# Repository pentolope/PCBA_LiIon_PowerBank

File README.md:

# Single-Cell Li-Ion Power Bank

Single-cell Li-ion power bank board: USB-C input, battery charging and protection, and a regulated 5 V output capable of at least 2 A.

This repository holds the design problem for `PCBA_LiIon_PowerBank`, a single-cell Li-ion power bank board. The brief fixes the functional envelope: a USB-C input, battery charging, battery protection, a regulated 5 V output capable of at least 2 A, fuel/status indication, and a pushbutton-controlled output enable. It also states two process constraints — choose an integrated charger/power-path/boost solution where practical, and respect the layout guidance of the selected power ICs while minimizing high-current loop area — and instructs that stated requirements be treated as authoritative. Everything else is open: the brief names no part, vendor, IC, connector, cell, capacity, dimension, charge current, input power level, output-stage topology, stackup, or protection topology, so the architecture and every component choice belong to the design agent. At brief detail 2/5, the correct response is to make and document those decisions from cited evidence rather than to treat any of them as pre-fixed.

> **This board has not been designed.** There is no schematic, no layout and no
> part selection here — only the brief, a reading of the brief, and the
> scaffolding a design run needs. That is the intended state of this repository,
> not a gap in it.

## What the brief fixes, and what it leaves open

The brief pins down 13 requirements and deliberately leaves
19 decisions to whoever designs the board. The `Source` column says
which is which: `brief` is quoted from [BRIEF.md](BRIEF.md), `metadata` comes
from the benchmark catalogue, and `open` means the brief does not fix it.

| Aspect | Value | Source |
|---|---|---|
| Board function | Single-cell Li-ion power bank board | brief |
| Input interface | USB-C input | brief |
| Charging | Battery charging on the board | brief |
| Battery protection | Battery protection required (location and topology unstated) | brief |
| Output rail | Regulated 5 V, capable of at least 2 A | brief |
| Indication | Fuel/status indication (form not specified) | brief |
| User control | Pushbutton-controlled output enable | brief |
| Power IC integration preference | Integrated charger/power-path/boost solution where practical (a preference, with "practical" left undefined) | brief |
| Layout constraint | Follow the selected power ICs' layout guidance; minimize high-current loop area | brief |
| Requirement authority | Stated requirements are authoritative; where the brief is open, the agent makes and documents the decision | brief |
| Toolkit relationship | Repo consumes the shared PCBA_AutoDesignAndTest toolkit; no board-specific logic added to the toolkit | brief |
| Likely layer count | 2 or 4 (stated as "likely" in both the brief header and metadata; fixed by neither) | metadata |
| Category / difficulty / brief detail | power-management; difficulty 2; detail 2 | metadata |
| Primary stressors | charger layout, power-path routing, battery safety, USB-C power | metadata |
| Parts, connectors, cell, mechanics, charge current, input power level, output-stage and protection topology | Not fixed by the brief — design agent's choice | open |

The full split, with the verbatim brief text substantiating every fixed
requirement, is in [board/requirements.md](board/requirements.md) and
machine-readably in [board/requirements.json](board/requirements.json).

**Missing details are design freedom, not permission to fabricate unstated user
requirements.** A choice the brief left open is recorded as a decision, with its
reasoning — never promoted into a requirement.

## Benchmark position

| | |
|---|---|
| Benchmark id | 7 of 32 |
| Category | power-management |
| Difficulty | 2 / 5 |
| Brief detail | 2 / 5 |
| Likely layer count | 2 or 4 |
| Primary stressors | charger layout, power-path routing, battery safety, USB-C power |

This is a difficulty-2, detail-2 power-management board whose stressors are charger layout, power-path routing, battery safety, and USB-C power. It tests whether an agent can turn a short functional brief into a defensible power chain — sizing, selecting, and laying out a charger, a power path, and a 5 V output stage — and whether it can substantiate a 2 A output claim with real datasheet, magnetics, and thermal evidence instead of asserting it. Because the brief names no parts and no mechanics, it equally tests whether the agent keeps its own choices visible as choices rather than smuggling them in as requirements.

This repository is one of thirty-two. The suite, the protocol and the results
live in [PCBA_AutoDesignAndTest_Bench](https://github.com/pentolope/PCBA_AutoDesignAndTest_Bench).

## Repository layout

| Path | Contents |
|---|---|
| `BRIEF.md` | the supplied brief — authoritative, preserved byte for byte, never edited |
| `board/requirements.md` | what the brief fixes, what it leaves open, and where decisions get recorded |
| `board/requirements.json` | the same split, machine-readable, each fixed requirement bound to brief text |
| `board/manifest.template.json` | the toolkit's minimum manifest, pre-filled for this board |
| `board/toolchain.json` | where this board's build finds KiCad and the router |
| `benchmark/metadata.json` | the supplied catalogue entry — category, difficulty, detail, stressors |
| `docs/architecture.md` | the decisions this board must make, as questions, unanswered |
| `docs/sources.md` | the classes of evidence the design will have to cite |
| `docs/status.md` | what exists, what does not, and what is deliberately absent |
| `candidates/` | disposable search output, ignored by Git |
| `.claude/skills/` | the accountability-review skill [CLAUDE.md](CLAUDE.md) requires before a push |
| `tooling/PCBA_AutoDesignAndTest` | the shared verification/routing/release toolkit, as a pinned submodule |

## Getting the repository

The toolkit is a submodule and carries KiCad Routing Tools as a submodule of its
own, so clone recursively:

```bash
git clone --recursive https://github.com/pentolope/PCBA_LiIon_PowerBank.git
```

```bash
git submodule update --init --recursive
```

## Designing the board

Generic verification, routing and release logic is **not** written here. It is
consumed from `tooling/PCBA_AutoDesignAndTest`, which is board-agnostic by
construction and must stay that way; this repository owns the board and nothing
else. Start from
[the toolkit's onboarding guide](tooling/PCBA_AutoDesignAndTest/examples/onboarding.md),
and see [CLAUDE.md](CLAUDE.md) for the rules a design run works under.

```bash
python3 tooling/PCBA_AutoDesignAndTest/run.py preflight
```

## Brief integrity

`BRIEF.md` SHA-256 `a83c2729b4cd3572342d1c0d042245c18bb77970d150b0bb1acddd78cdec8627`

Every quotation in `board/requirements.json` is bound to those exact bytes. If
the brief ever changes, the bindings are stale by construction — which is the
point of recording the digest.

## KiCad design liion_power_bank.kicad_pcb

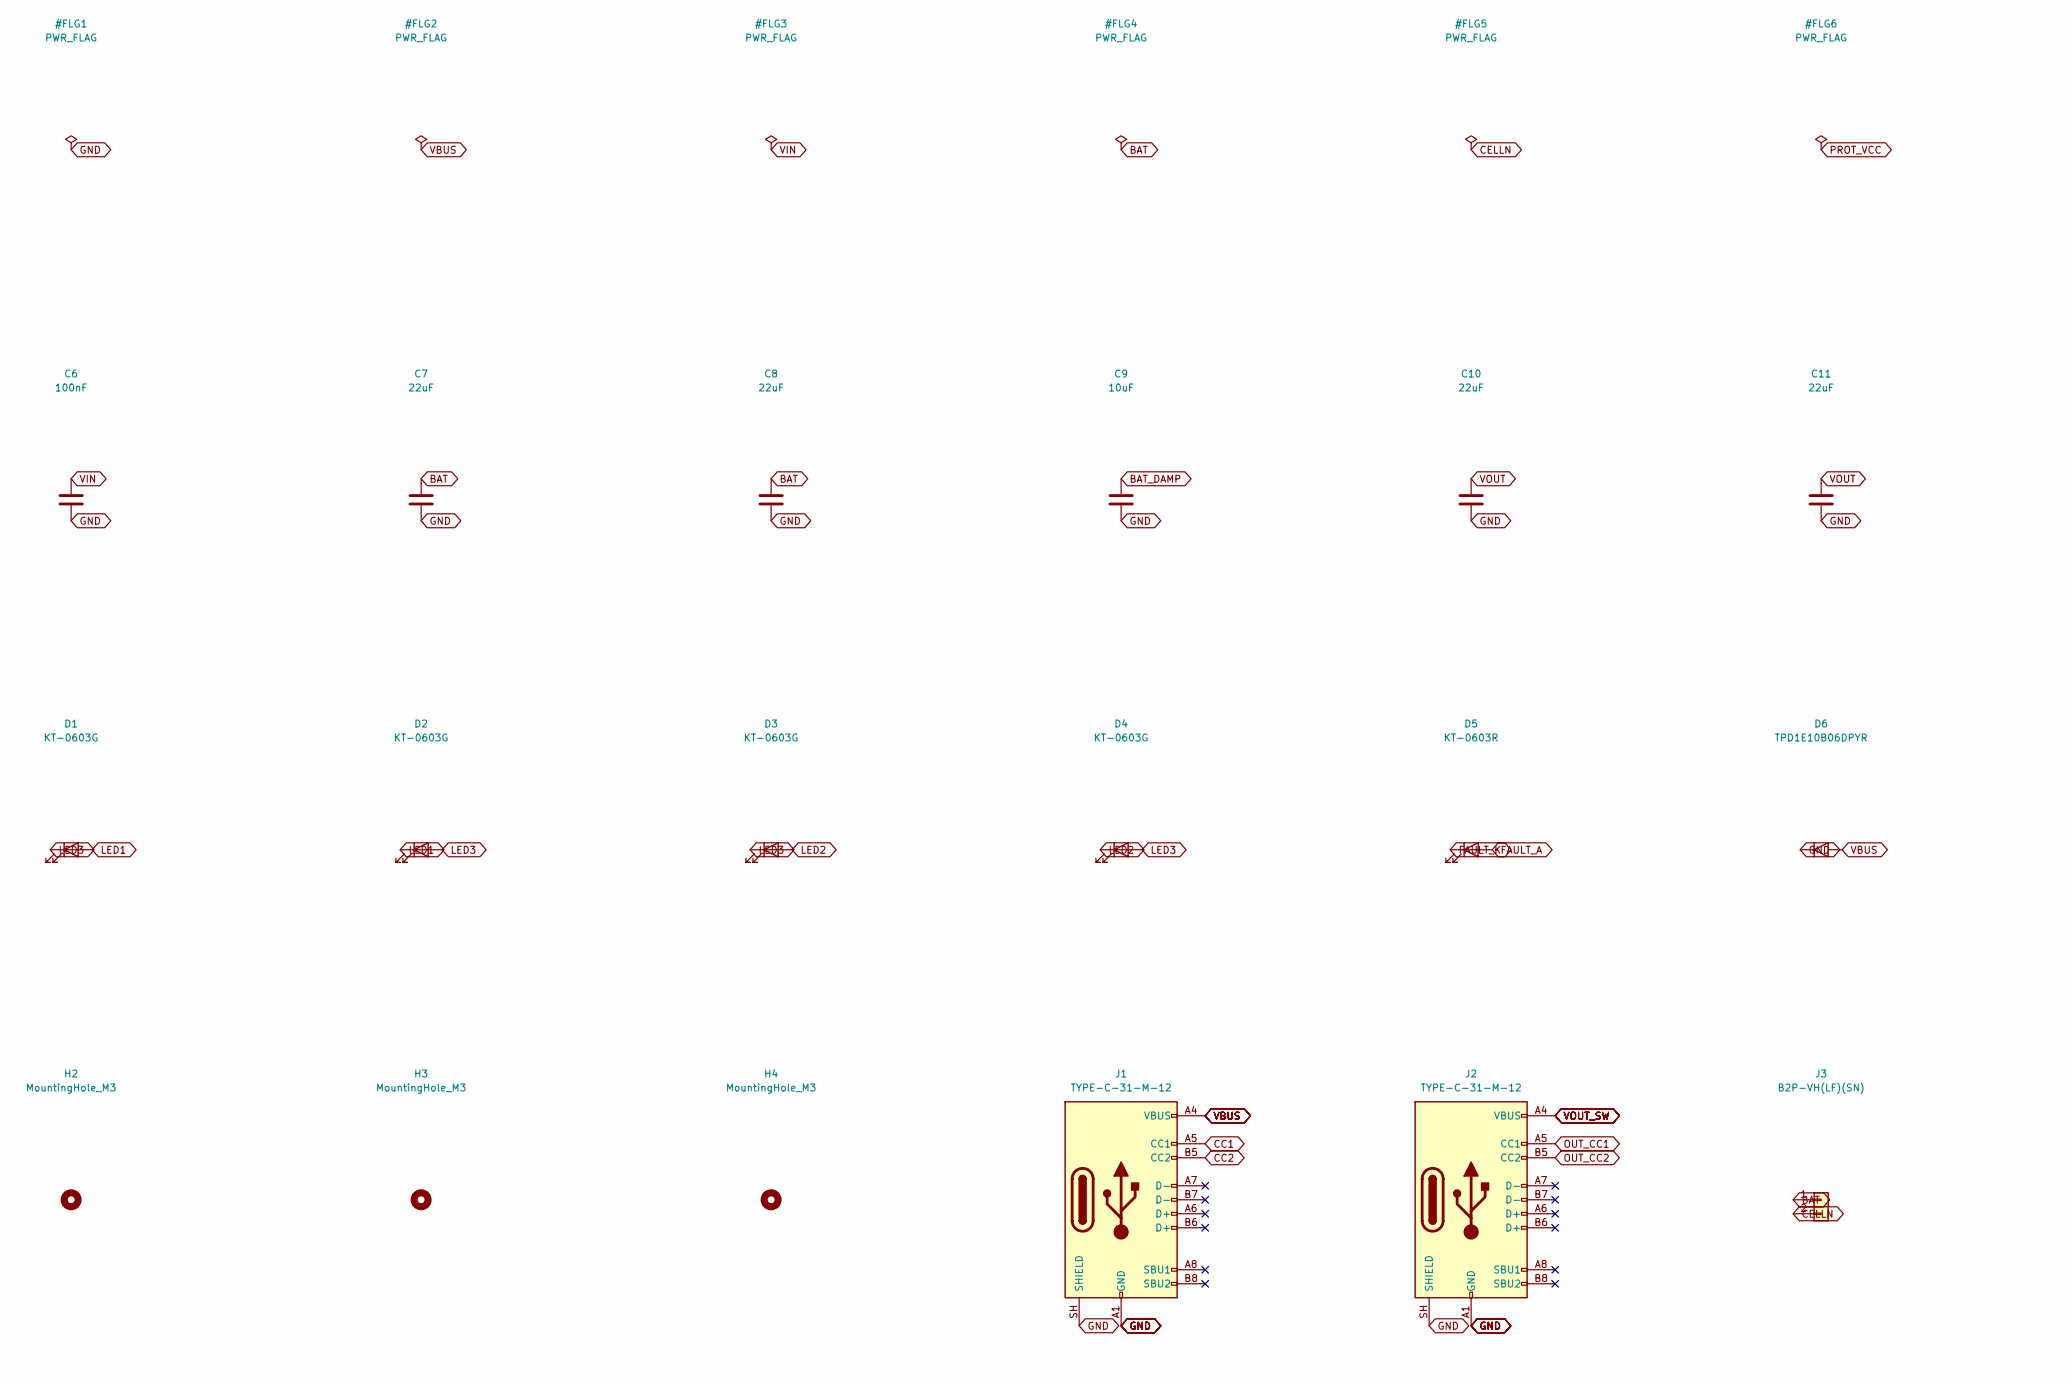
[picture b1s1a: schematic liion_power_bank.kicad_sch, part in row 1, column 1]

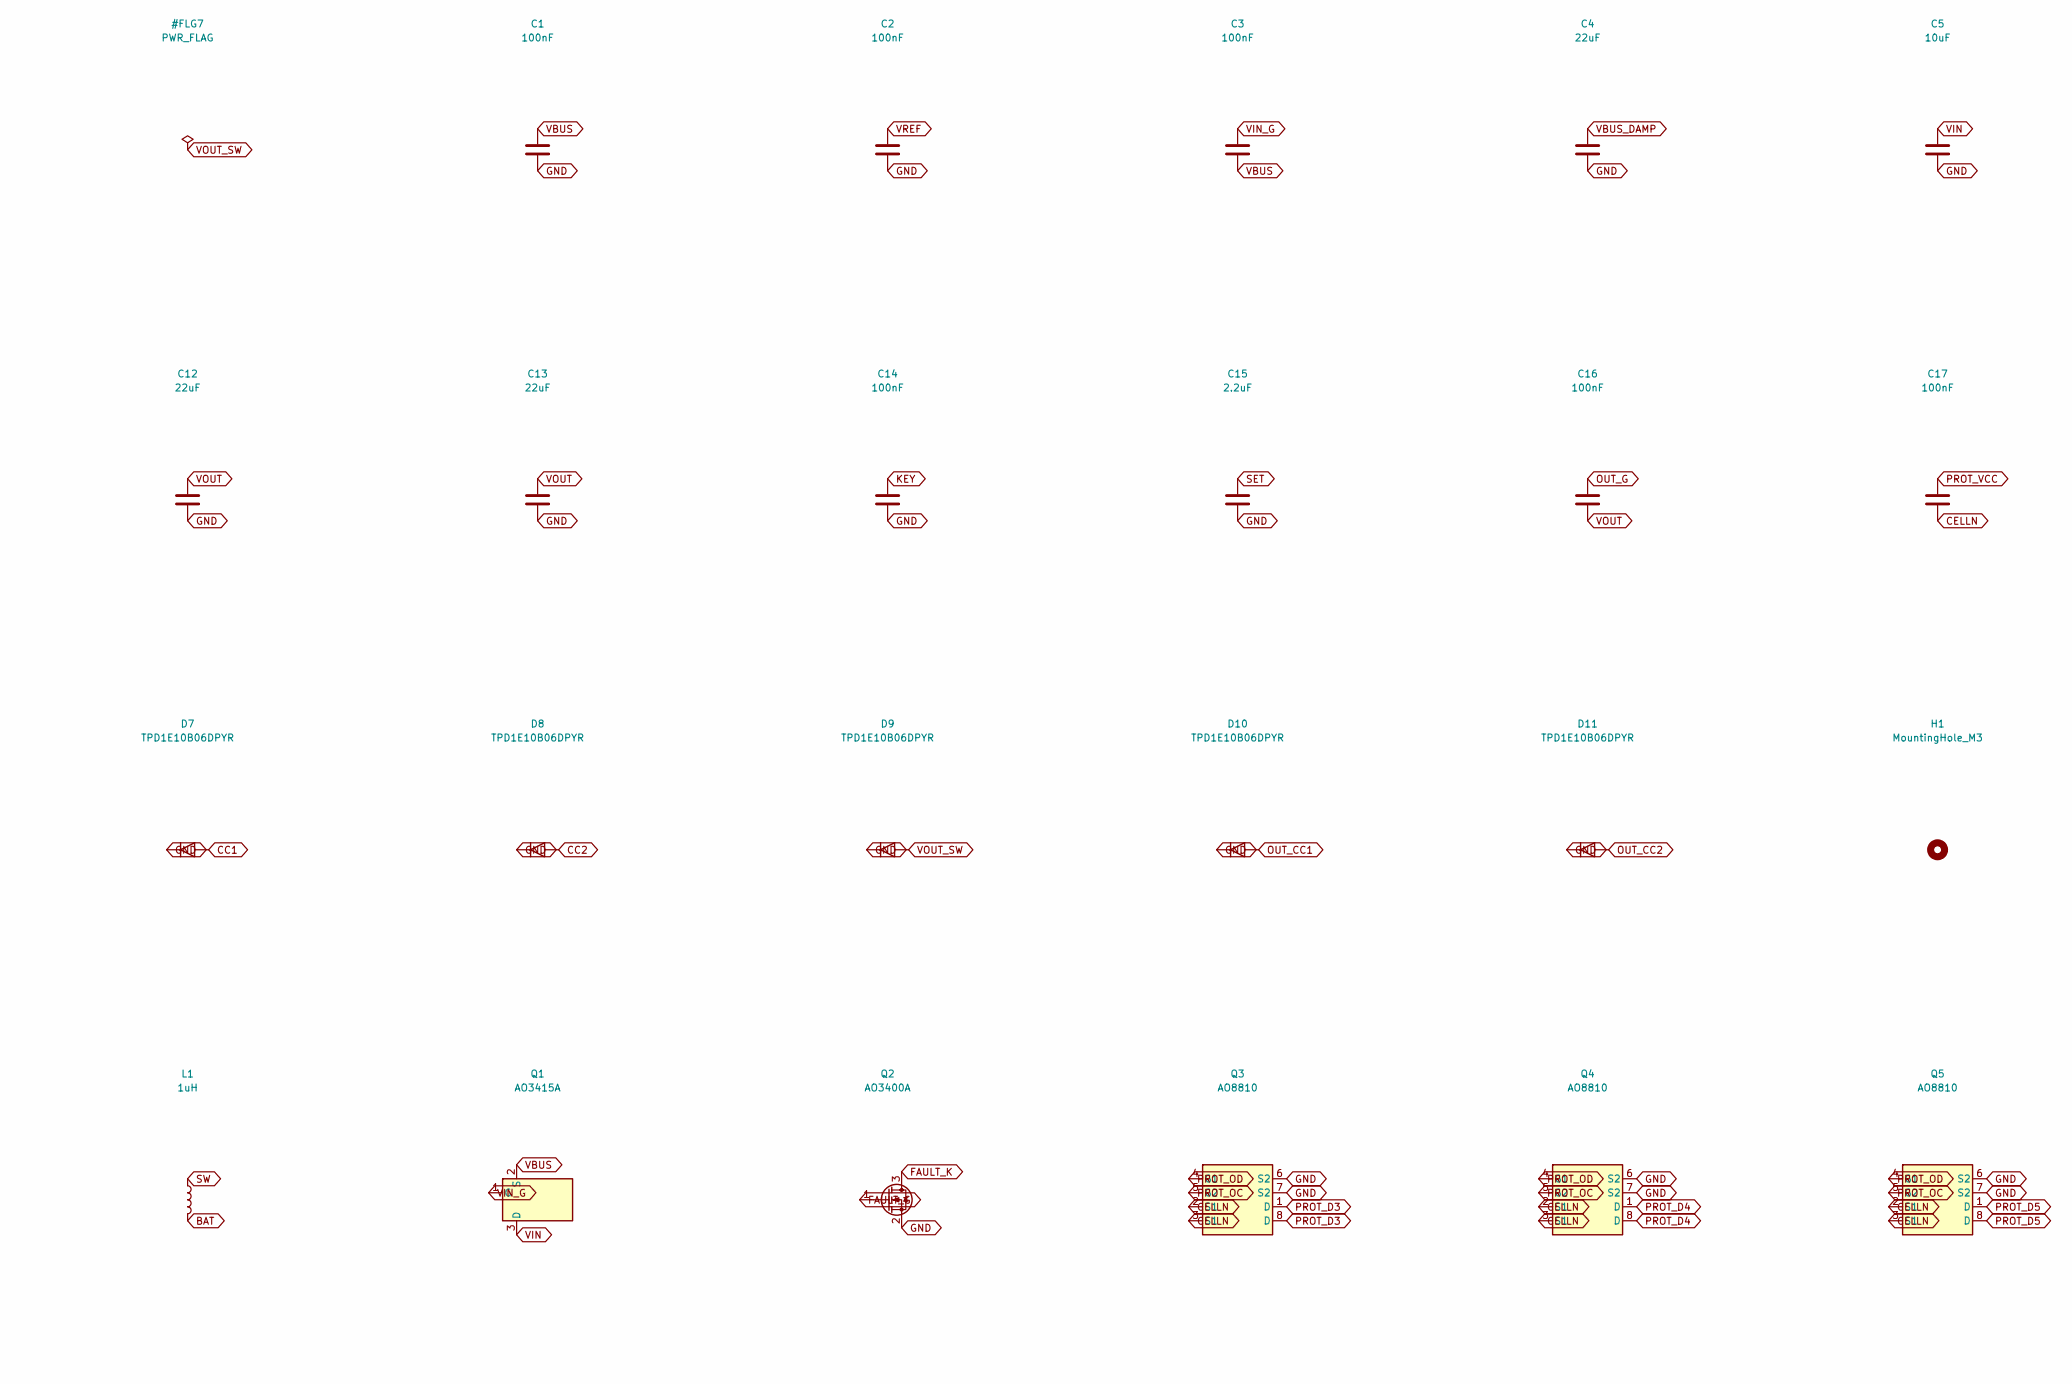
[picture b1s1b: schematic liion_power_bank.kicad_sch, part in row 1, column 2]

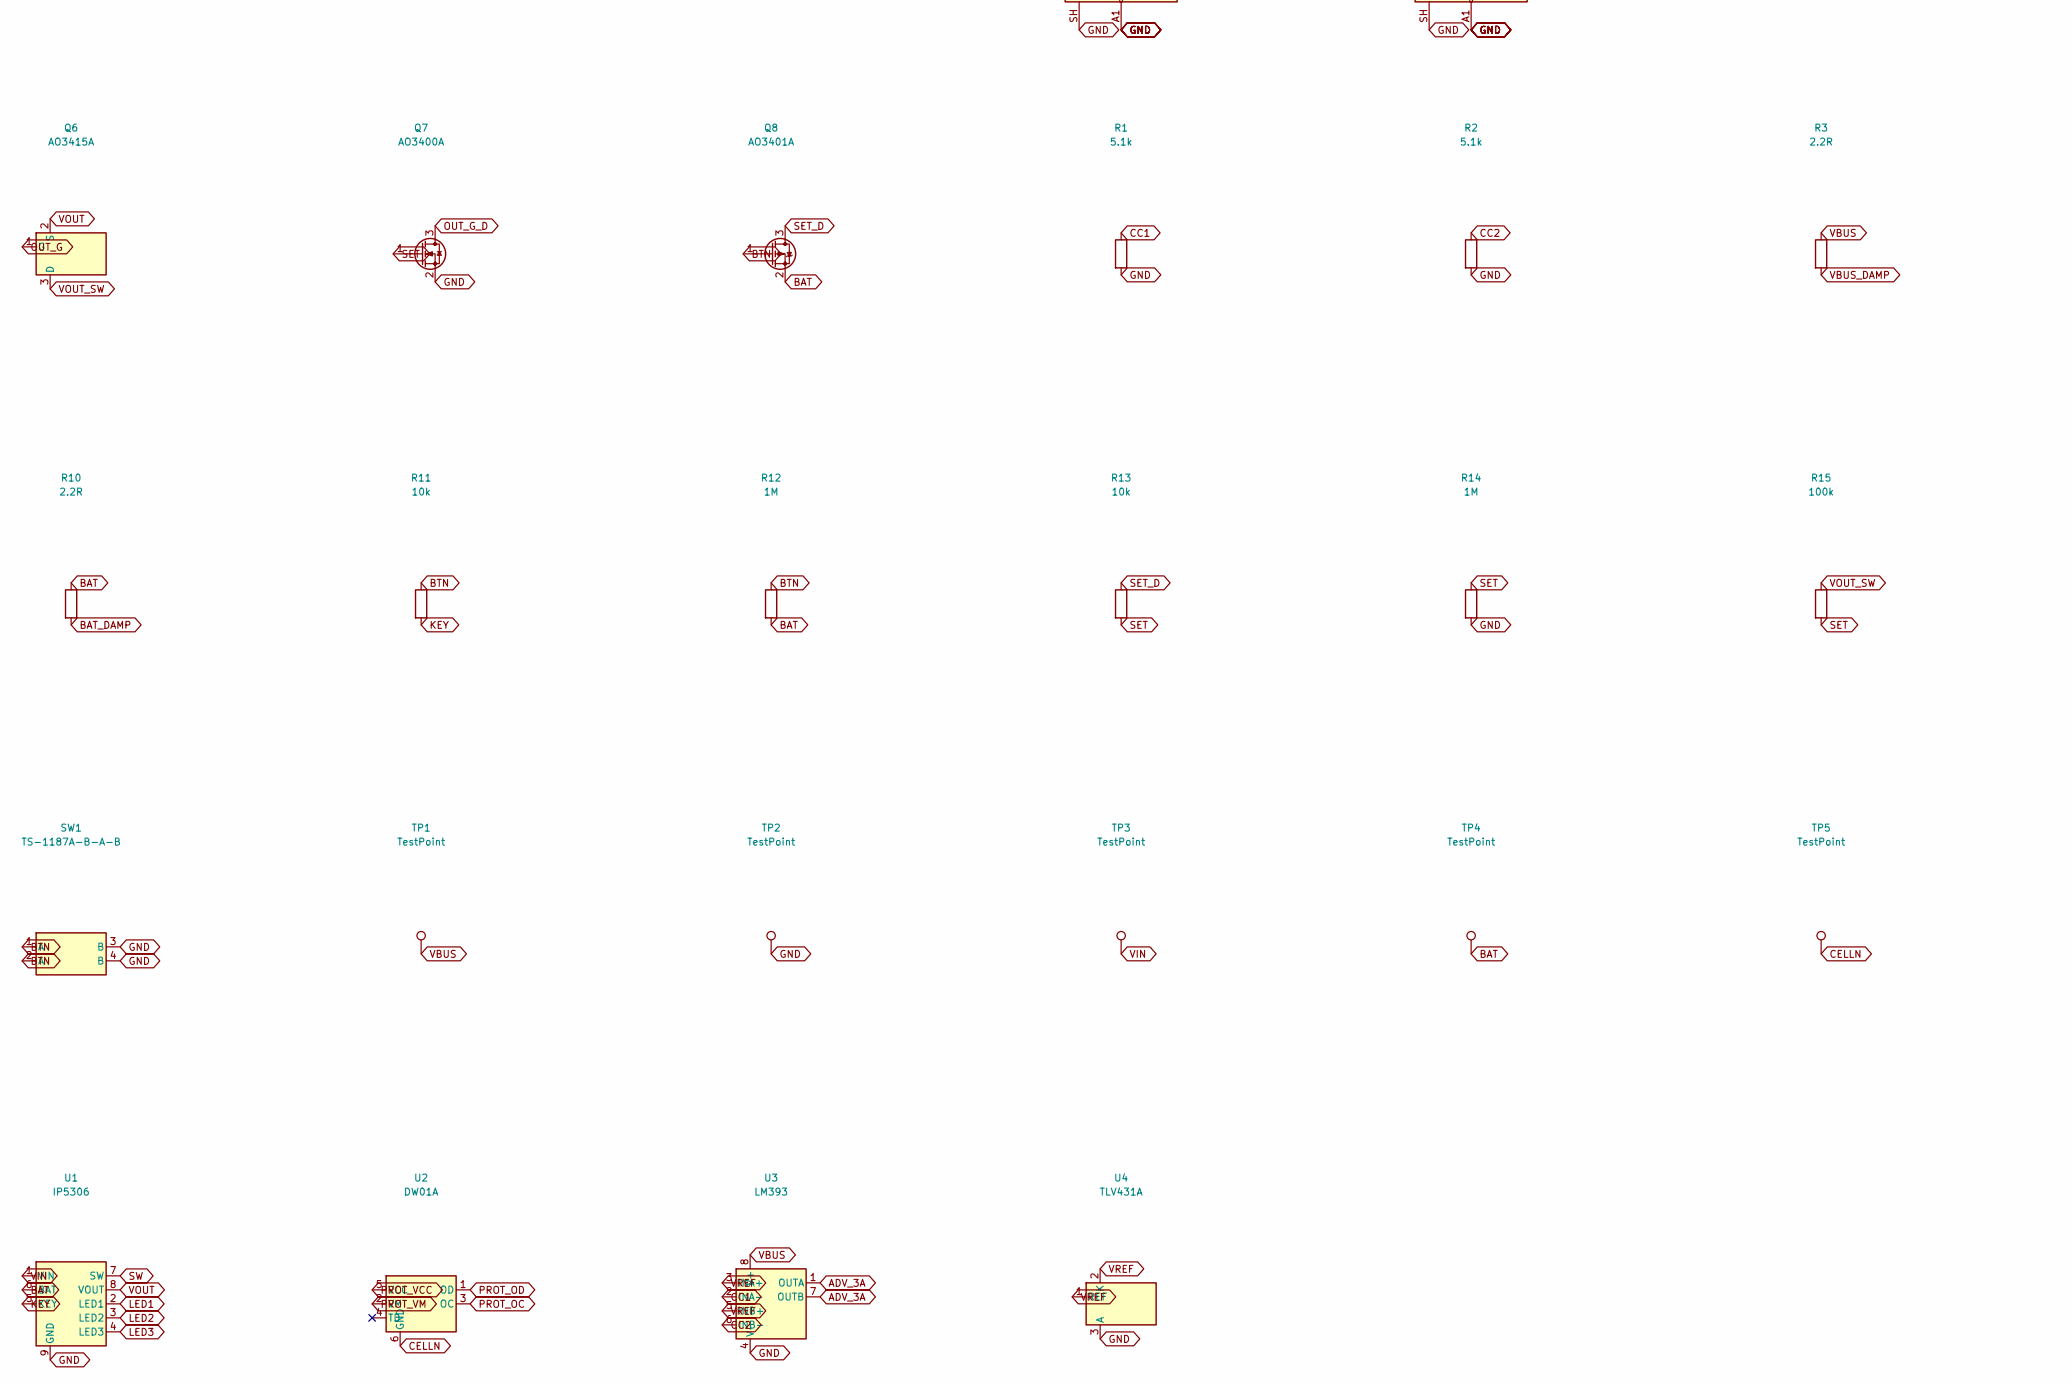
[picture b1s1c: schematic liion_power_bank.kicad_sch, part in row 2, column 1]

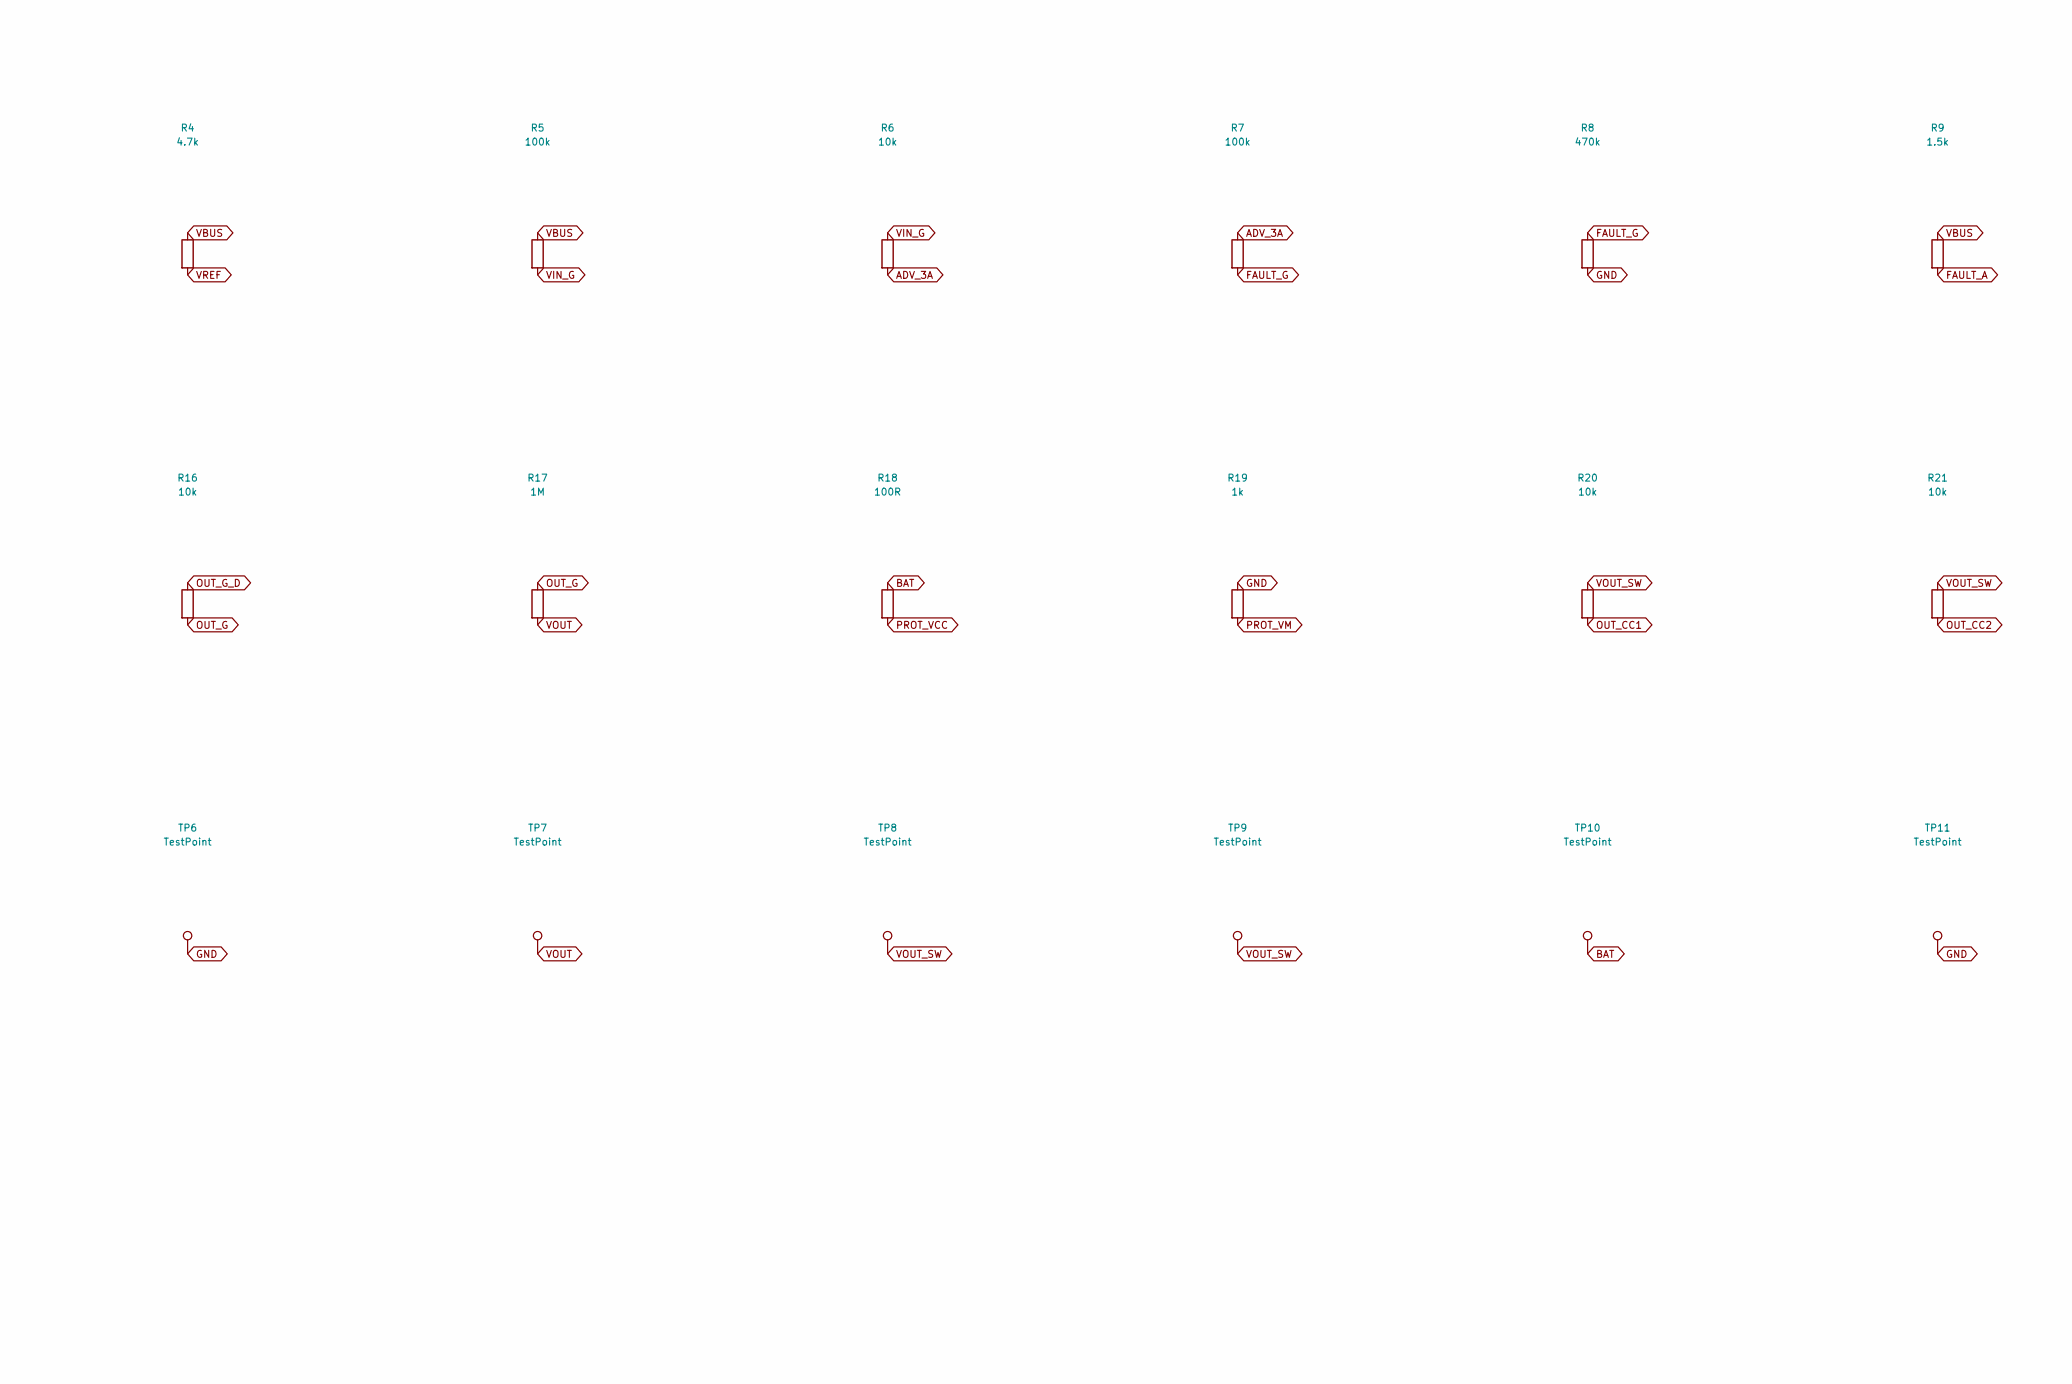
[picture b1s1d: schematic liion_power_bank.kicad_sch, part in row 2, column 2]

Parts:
C1, C2, C3, C6, C14, C16, C17: 100nF; C_0603_1608Metric; MPN CC0603KRX7R9BB104; LCSC C14663
C4, C7, C8, C10, C11, C12, C13: 22uF; C_1206_3216Metric; MPN TCC1206X5R226M250HT; LCSC C380359
C5, C9: 10uF; C_0805_2012Metric; MPN CL21A106KAYNNNE; LCSC C15850
C15: 2.2uF; C_0603_1608Metric; MPN CL10A225KO8NNNC; LCSC C23630
D1, D2, D3, D4: KT-0603G; LED_0603_1608Metric; MPN KT-0603G; LCSC C12624
D5: KT-0603R; LED_0603_1608Metric; MPN KT-0603R; LCSC C2286
D6, D7, D8, D9, D10, D11: TPD1E10B06DPYR; TI_X1SON-2_1.0x0.6mm_P0.65mm; MPN TPD1E10B06DPYR; LCSC C48260
H1, H2, H3, H4: MountingHole_M3; MountingHole_3.2mm_M3
J1, J2: TYPE-C-31-M-12; USB_C_Receptacle_HRO_TYPE-C-31-M-12; MPN TYPE-C-31-M-12; LCSC C165948
J3: B2P-VH(LF)(SN); JST_VH_B2P-VH_1x02_P3.96mm_Vertical; MPN B2P-VH(LF)(SN); LCSC C160315
L1: 1uH; L_Sunlord_SWPA8040S; MPN SWPA8040S1R0NT; LCSC C96968
Q1, Q6: AO3415A; SOT-23; MPN AO3415A; LCSC C133233
Q2, Q7: AO3400A; SOT-23; MPN AO3400A; LCSC C20917
Q3, Q4, Q5: AO8810; TSSOP-8_3x3mm_P0.65mm; MPN AO8810; LCSC C21426
Q8: AO3401A; SOT-23; MPN AO3401A; LCSC C15127
R1, R2: 5.1k; R_0603_1608Metric; MPN 0603WAF5101T5E; LCSC C23186
R3, R10: 2.2R; R_0603_1608Metric; MPN 0603WAJ022JT5E; LCSC C25226
R4: 4.7k; R_0603_1608Metric; MPN 0603WAF4701T5E; LCSC C23162
R5, R7, R15: 100k; R_0603_1608Metric; MPN 0603WAF1003T5E; LCSC C25803
R6, R11, R13, R16, R20, R21: 10k; R_0603_1608Metric; MPN 0603WAF1002T5E; LCSC C25804
R8: 470k; R_0603_1608Metric; MPN 0603WAF4703T5E; LCSC C23178
R9: 1.5k; R_0603_1608Metric; MPN 0603WAF1501T5E; LCSC C22843
R12, R14, R17: 1M; R_0603_1608Metric; MPN 0603WAF1004T5E; LCSC C22935
R18: 100R; R_0603_1608Metric; MPN 0603WAF1000T5E; LCSC C22775
R19: 1k; R_0603_1608Metric; MPN 0603WAF1001T5E; LCSC C21190
SW1: TS-1187A-B-A-B; SW_TS-1187A_5.1x5.1mm; MPN TS-1187A-B-A-B; LCSC C318884
TP1, TP2, TP3, TP4, TP5, TP6, TP7, TP8, TP9, TP10, TP11: TestPoint; TestPoint_Pad_D1.0mm
U1: IP5306; ESOP-8_3.9x4.9mm_P1.27mm_EP2.09x2.09mm; MPN IP5306; LCSC C181692
U2: DW01A; SOT-23-6; MPN DW01A; LCSC C351410
U3: LM393; SOIC-8_3.9x4.9mm_P1.27mm; MPN LM393DR2G; LCSC C7955
U4: TLV431A; SOT-23; MPN TLV431AIDBZR; LCSC C56765

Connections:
ADV_3A: R6.2, R7.1, U3.1 (OUTA), U3.7 (OUTB)
BAT: C7.1, C8.1, J3.1, L1.2, Q8.2 (S), R10.1, R12.2, R18.1, TP4.1, TP10.1, U1.6 (BAT)
BAT_DAMP: C9.1, R10.2
BTN: Q8.1 (G), R11.1, R12.1, SW1.1 (A), SW1.2 (A)
CC1: D7.2 (A), J1.A5 (CC1), R1.1, U3.2 (INA-)
CC2: D8.2 (A), J1.B5 (CC2), R2.1, U3.6 (INB-)
CELLN: C17.2, J3.2, Q3.2 (S1), Q3.3 (S1), Q4.2 (S1), Q4.3 (S1), Q5.2 (S1), Q5.3 (S1), TP5.1, U2.6 (GND)
FAULT_A: D5.2 (A), R9.2
FAULT_G: Q2.1 (G), R7.2, R8.1
FAULT_K: D5.1 (K), Q2.3 (D)
GND: C1.2, C2.2, C4.2, C5.2, C6.2, C7.2, C8.2, C9.2, C10.2, C11.2, C12.2, C13.2, C14.2, C15.2, D6.1 (K), D7.1 (K), D8.1 (K), D9.1 (K), D10.1 (K), D11.1 (K), J1.A1 (GND), J1.A12 (GND), J1.B1 (GND), J1.B12 (GND), J1.SH (SHIELD), J2.A1 (GND), J2.A12 (GND), J2.B1 (GND), J2.B12 (GND), J2.SH (SHIELD), Q2.2 (S), Q3.6 (S2), Q3.7 (S2), Q4.6 (S2), Q4.7 (S2), Q5.6 (S2), Q5.7 (S2), Q7.2 (S), R1.2, R2.2, R8.2, R14.2, R19.1, SW1.3 (B), SW1.4 (B), TP2.1, TP6.1, TP11.1, U1.9 (GND), U3.4 (V-), U4.3 (A)
KEY: C14.1, R11.2, U1.5 (KEY)
LED1: D1.2 (A), D2.1 (K), U1.2 (LED1)
LED2: D3.2 (A), D4.1 (K), U1.3 (LED2)
LED3: D1.1 (K), D2.2 (A), D3.1 (K), D4.2 (A), U1.4 (LED3)
OUT_CC1: D10.2 (A), J2.A5 (CC1), R20.2
OUT_CC2: D11.2 (A), J2.B5 (CC2), R21.2
OUT_G: C16.1, Q6.1 (G), R16.2, R17.1
OUT_G_D: Q7.3 (D), R16.1
PROT_D3: Q3.1 (D), Q3.8 (D)
PROT_D4: Q4.1 (D), Q4.8 (D)
PROT_D5: Q5.1 (D), Q5.8 (D)
PROT_OC: Q3.5 (G2), Q4.5 (G2), Q5.5 (G2), U2.3 (OC)
PROT_OD: Q3.4 (G1), Q4.4 (G1), Q5.4 (G1), U2.1 (OD)
PROT_VCC: C17.1, R18.2, U2.5 (VCC)
PROT_VM: R19.2, U2.2 (VM)
SET: C15.1, Q7.1 (G), R13.2, R14.1, R15.2
SET_D: Q8.3 (D), R13.1
SW: L1.1, U1.7 (SW)
VBUS: C1.1, C3.2, D6.2 (A), J1.A4 (VBUS), J1.A9 (VBUS), J1.B4 (VBUS), J1.B9 (VBUS), Q1.2 (S), R3.1, R4.1, R5.1, R9.1, TP1.1, U3.8 (V+)
VBUS_DAMP: C4.1, R3.2
VIN: C5.1, C6.1, Q1.3 (D), TP3.1, U1.1 (VIN)
VIN_G: C3.1, Q1.1 (G), R5.2, R6.1
VOUT: C10.1, C11.1, C12.1, C13.1, C16.2, Q6.2 (S), R17.2, TP7.1, U1.8 (VOUT)
VOUT_SW: D9.2 (A), J2.A4 (VBUS), J2.A9 (VBUS), J2.B4 (VBUS), J2.B9 (VBUS), Q6.3 (D), R15.1, R20.1, R21.1, TP8.1, TP9.1
VREF: C2.1, R4.2, U3.3 (INA+), U3.5 (INB+), U4.1 (REF), U4.2 (K)

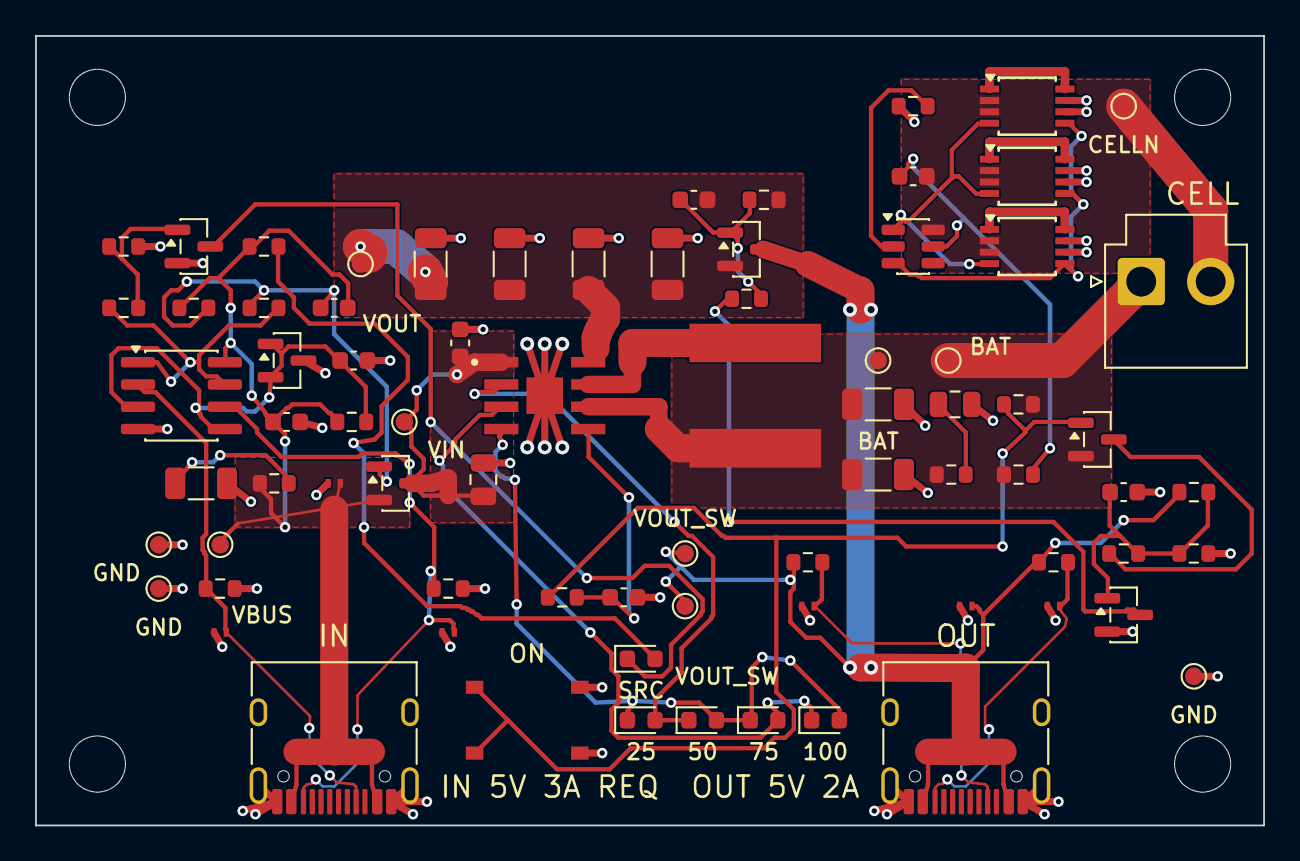
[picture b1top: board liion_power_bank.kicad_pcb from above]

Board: 2 copper layers, 70.0 x 45.0 mm, 81 parts (0 on the bottom side), 36 nets.

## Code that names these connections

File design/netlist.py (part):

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
#: IP5306 package pins by name. The thermal pad is the device's ground
#: connection, so it is a numbered pin here and not a mechanical feature.
IP5306_PINS = {"VIN": "1", "LED1": "2", "LED2": "3", "LED3": "4",
               "KEY": "5", "BAT": "6", "SW": "7", "VOUT": "8", "GND": "9"}

#: DW01A package pins by name.
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
    #: The cell's positive terminal. Every part on it is rated above the
    #: highest voltage the protection device allows the cell to reach.
    bat = ["J3.1", "U1.%s" % IP5306_PINS["BAT"], "L1.2", "C7.1", "C8.1",
           "R10.1", "R18.1", "Q8.2", "R12.2", "TP4.1", "TP10.1",
           "#FLG4.1"]

    #: The cell's negative terminal, inside the protection switch.
    celln = ["J3.2", "U2.%s" % DW01A_PINS["GND"], "C17.2", "TP5.1",
             "#FLG5.1"]

    #: The converter output, ahead of the enable switch.
    vout = ["U1.%s" % IP5306_PINS["VOUT"], "C10.1", "C11.1", "C12.1",
            "C13.1", "Q6.2", "R17.2", "C16.2", "TP7.1"]

    #: The output port's supply, behind the enable switch.
    vout_sw = ["Q6.3", "R15.1", "R20.1", "R21.1", "D9.2",
               "TP8.1", "TP9.1", "#FLG7.1"]
    for pin in USB_C_PINS["VBUS"]:
        vout_sw.append("J2.%s" % pin)

    nets = {
        "GND": ground,
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        "VREF": ["R4.2", "C2.1", "U4.1", "U4.2",
                 "U3.%s" % LM393_PINS["INA+"],
                 "U3.%s" % LM393_PINS["INB+"]],
        "ADV_3A": ["U3.%s" % LM393_PINS["OUTA"],
                   "U3.%s" % LM393_PINS["OUTB"], "R6.2", "R7.1"],
        # input switch gate, and the damper across the source
        "VIN_G": ["Q1.1", "R5.2", "R6.1", "C3.1"],
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        "BAT_DAMP": ["R10.2", "C9.1"],
        # state-of-charge indicators: four across three drivers, in
        # antiparallel pairs, as the controller's own reference wires them
        "LED1": ["U1.%s" % IP5306_PINS["LED1"], "D1.2", "D2.1"],
        "LED2": ["U1.%s" % IP5306_PINS["LED2"], "D3.2", "D4.1"],
        "LED3": ["U1.%s" % IP5306_PINS["LED3"], "D1.1", "D2.2", "D3.1",
                 "D4.2"],
        # push button
        "BTN": ["SW1.1", "SW1.2", "R11.1", "R12.1", "Q8.1"],
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        "OUT_G_D": ["Q7.3", "R16.1"],
        "OUT_G": ["R16.2", "R17.1", "C16.1", "Q6.1"],
        # cell protection
        "PROT_VCC": ["R18.2", "U2.%s" % DW01A_PINS["VCC"], "C17.1",
                     "#FLG6.1"],
        "PROT_OD": ["U2.%s" % DW01A_PINS["OD"]],
        "PROT_OC": ["U2.%s" % DW01A_PINS["OC"]],
        "PROT_VM": ["U2.%s" % DW01A_PINS["VM"], "R19.2"],
        # what the output port advertises
        "OUT_CC1": ["J2.A5", "R20.2", "D10.2"],
        "OUT_CC2": ["J2.B5", "R21.2", "D11.2"],
    }
    for index in range(3, 3 + PROTECTION_PACKAGES):
        for pin in AO8810_PINS["S1"]:
            nets["CELLN"].append("Q%d.%s" % (index, pin))
        for pin in AO8810_PINS["S2"]:
            nets["GND"].append("Q%d.%s" % (index, pin))
        # Each package's two drains are common inside it, so they are one
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        # package, and the packages already share the current at both ends.
        nets["PROT_D%d" % index] = ["Q%d.%s" % (index, pin)
                                    for pin in AO8810_PINS["D"]]
        nets["PROT_OD"].append("Q%d.%s" % (index, AO8810_PINS["G1"]))
        nets["PROT_OC"].append("Q%d.%s" % (index, AO8810_PINS["G2"]))
    return nets


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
